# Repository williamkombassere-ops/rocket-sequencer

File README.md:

# 🚀 Rocket Sequencer (AEROTECH)

Séquenceur électronique de vol conçu pour des projets de fuséonautique (AEROTECH). 

## 🛠️ Fonctionnalités
* Gestion des allumages et des phases de vol.
* Conception électronique réalisée sous KiCad.
* Intégration de fichiers 3D pour la structure (`.step`).

## 📁 Structure du projet
* `Gerber_Finale/` : Fichiers de fabrication pour le PCB.
* `Séquenceur-backups/` : Sauversions et historiques du projet KiCad.
* `Séquenceur.kicad_pcb` : Fichier du circuit imprimé.
* `Séquenceur.kicad_sch` : Schéma électrique.

## 💻 Logiciels utilisés
* [KiCad](https://www.kicad.org/) pour la conception de la carte.

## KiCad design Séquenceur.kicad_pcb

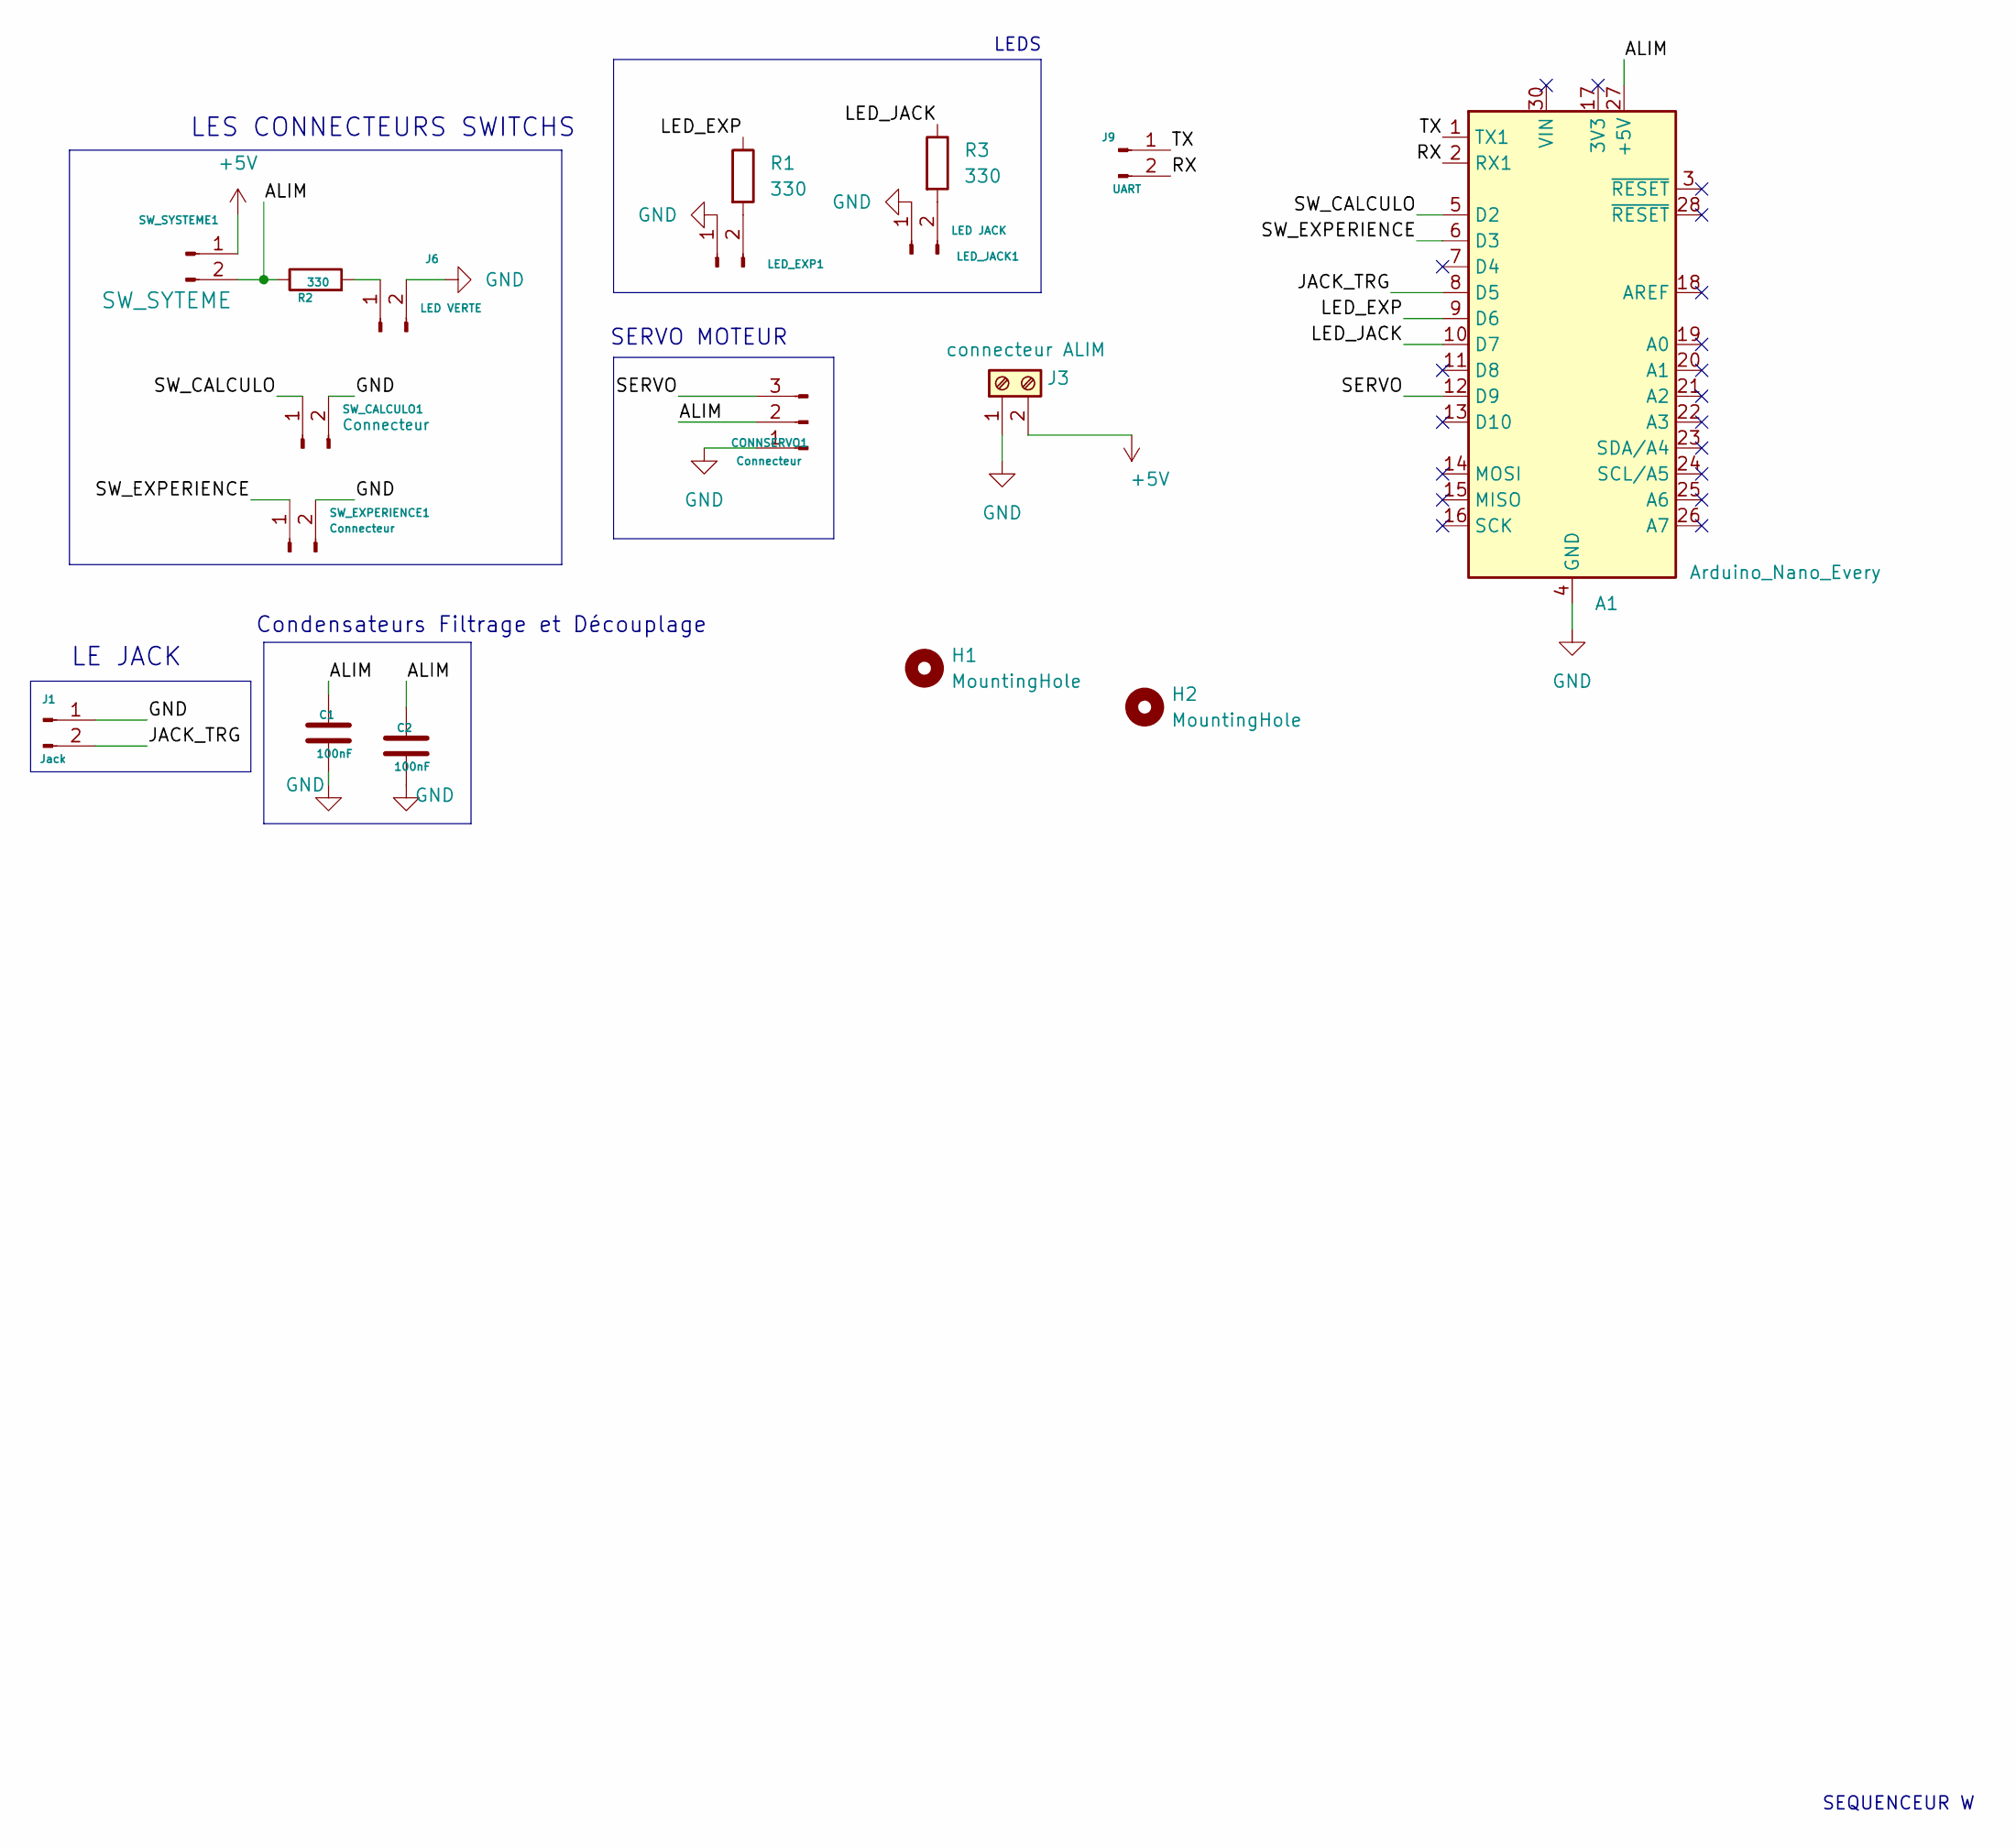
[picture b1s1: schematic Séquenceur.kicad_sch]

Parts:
A1: Arduino_Nano_Every; Arduino_Nano
C1, C2: 100nF; C_Rect_L7.0mm_W2.5mm_P5.00mm
CONNSERVO1: Connecteur; JST_XH_B3B-XH-A_1x03_P2.50mm_Vertical
H1, H2: MountingHole; MountingHole_3.2mm_M3
J1: Jack; JST_XH_B2B-XH-A_1x02_P2.50mm_Vertical
J3: connecteur ALIM; TerminalBlock_Phoenix_PT-1,5-2-5.0-H_1x02_P5.00mm_Horizontal
J6: LED VERTE; JST_XH_B2B-XH-A_1x02_P2.50mm_Vertical
J9: UART; JST_XH_B2B-XH-A_1x02_P2.50mm_Vertical
LED_EXP1: J; JST_XH_B2B-XH-A_1x02_P2.50mm_Vertical
LED_JACK1: LED JACK; JST_XH_B2B-XH-A_1x02_P2.50mm_Vertical
R1, R2, R3: 330; R_Axial_DIN0207_L6.3mm_D2.5mm_P7.62mm_Horizontal
SW_CALCULO1: Connecteur; JST_XH_B2B-XH-A_1x02_P2.50mm_Vertical
SW_EXPERIENCE1: Connecteur; JST_XH_B2B-XH-A_1x02_P2.50mm_Vertical
SW_SYSTEME1: SW_SYTEME; JST_XH_B2B-XH-A_1x02_P2.50mm_Vertical

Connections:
+5V: J3.2, SW_SYSTEME1.1
/ALIM: A1.27 (+5V), C1.1, C2.1, CONNSERVO1.2, R2.1, SW_SYSTEME1.2
/JACK_TRG: A1.8 (D5), J1.2
/LED_EXP: A1.9 (D6), R1.1
/LED_JACK: A1.10 (D7), R3.1
/RX: A1.2 (RX1), J9.2
/SERVO: A1.12 (D9), CONNSERVO1.3
/SW_CALCULO: A1.5 (D2), SW_CALCULO1.1
/SW_EXPERIENCE: A1.6 (D3), SW_EXPERIENCE1.1
/TX: A1.1 (TX1), J9.1
GND: A1.4 (GND), A1.29 (GND), C1.2, C2.2, CONNSERVO1.1, J1.1, J3.1, J6.2, LED_EXP1.1, LED_JACK1.1, SW_CALCULO1.2, SW_EXPERIENCE1.2
unnamed: J6.1, R2.2
unnamed: LED_EXP1.2, R1.2
unnamed: LED_JACK1.2, R3.2

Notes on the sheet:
LE JACK
Condensateurs Filtrage et Découplage
SEQUENCEUR W
SERVO MOTEUR
LES CONNECTEURS SWITCHS
LEDS

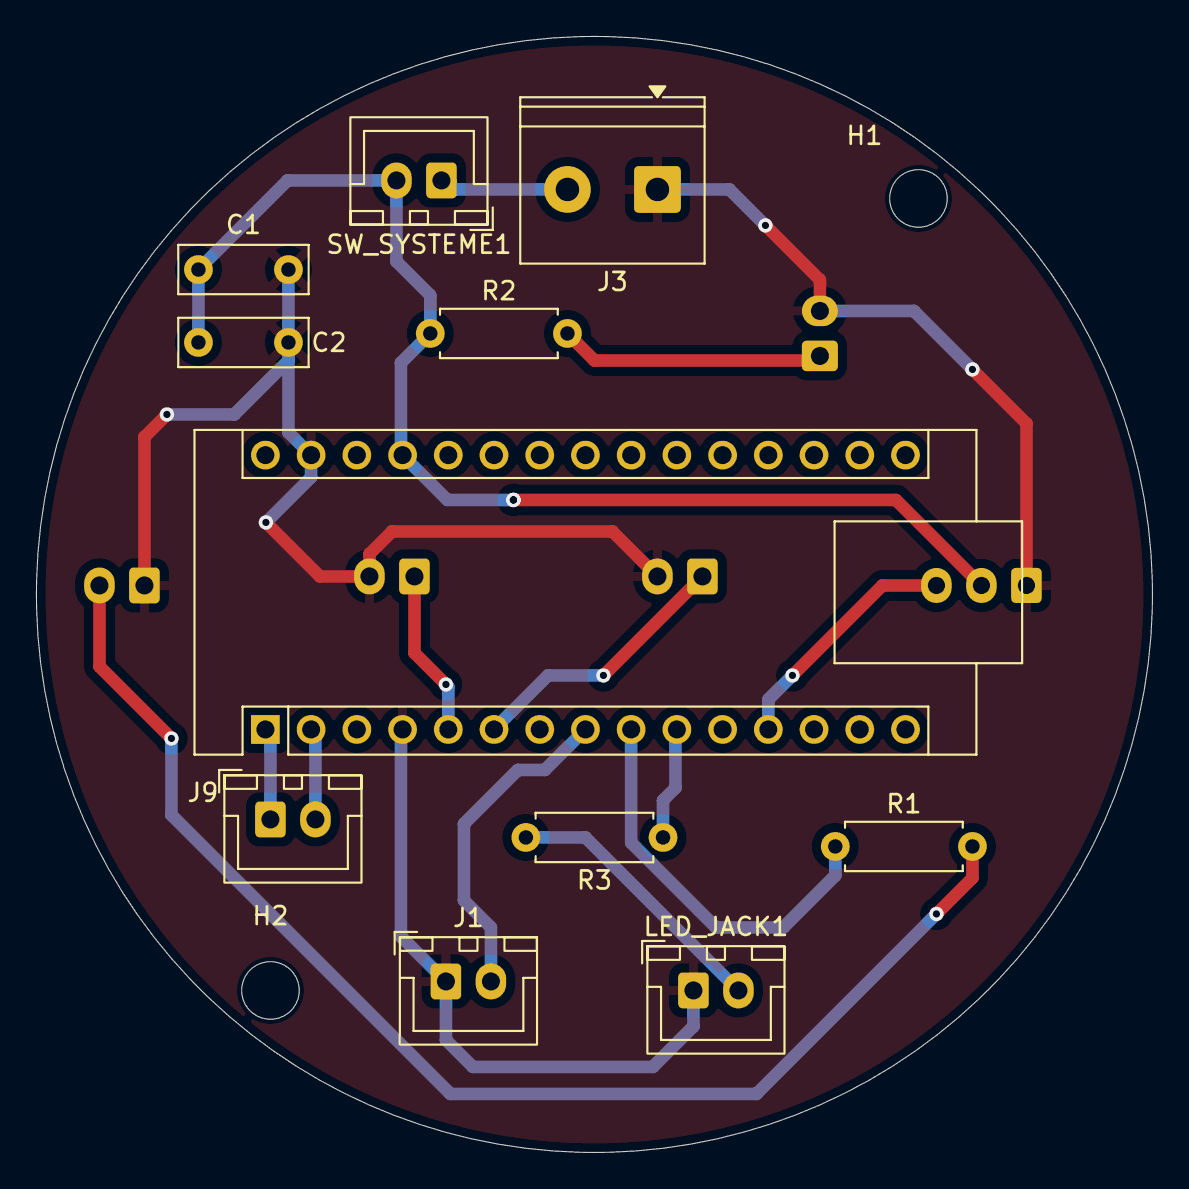
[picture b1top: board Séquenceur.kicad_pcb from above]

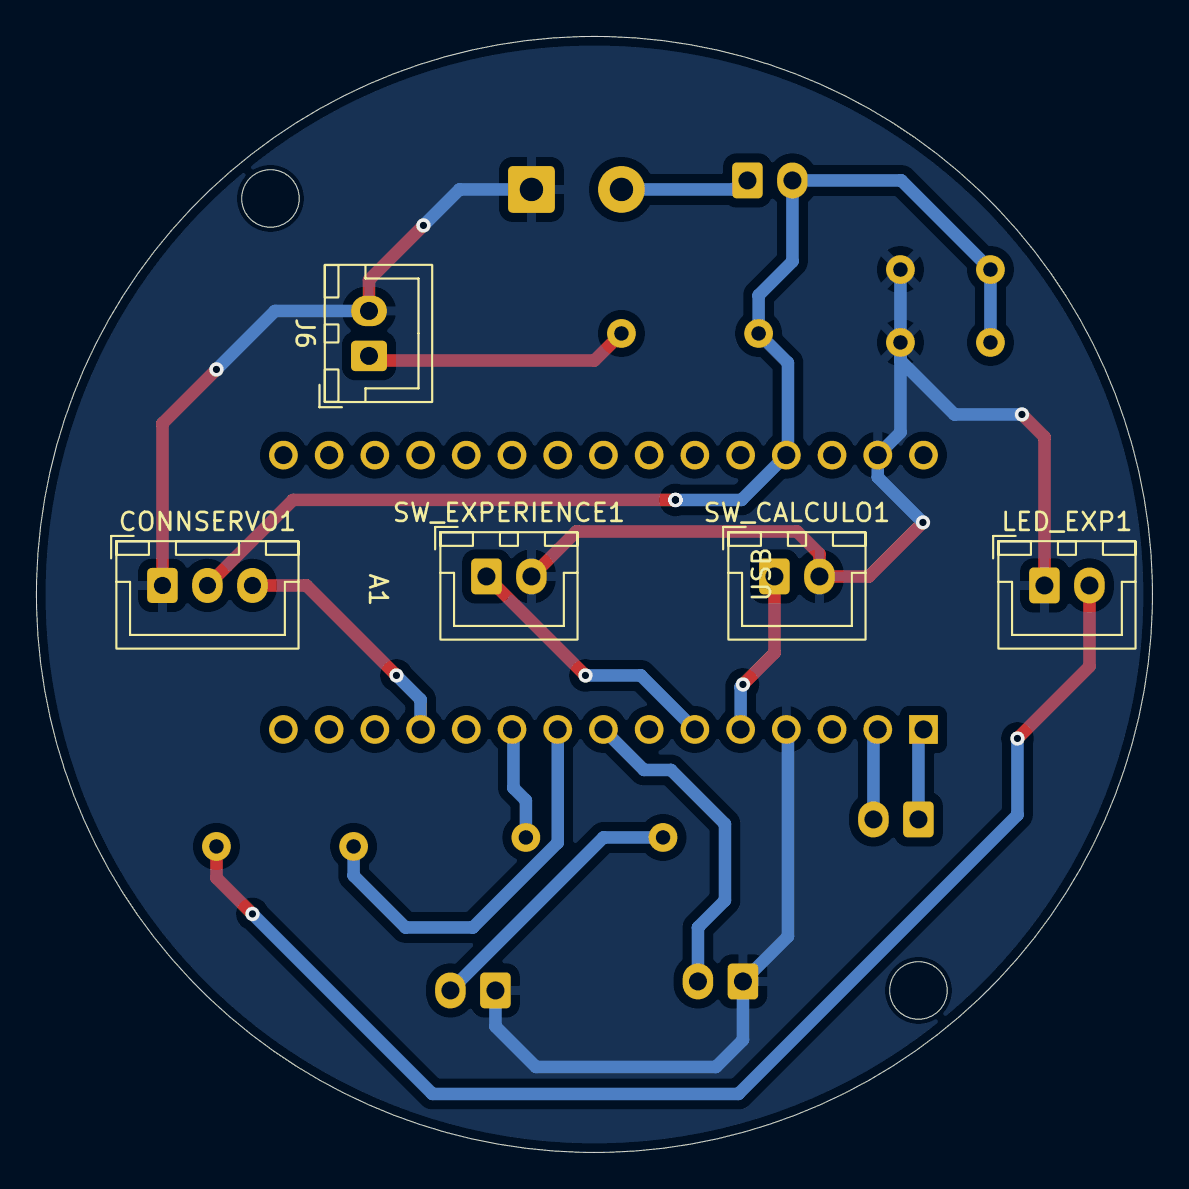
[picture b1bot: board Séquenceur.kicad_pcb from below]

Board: 2 copper layers, 62.0 x 62.0 mm, 18 parts (5 on the bottom side), 14 nets.
